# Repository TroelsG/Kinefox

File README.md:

# Kinefox
The wildlife tracker powered by kinetic energy

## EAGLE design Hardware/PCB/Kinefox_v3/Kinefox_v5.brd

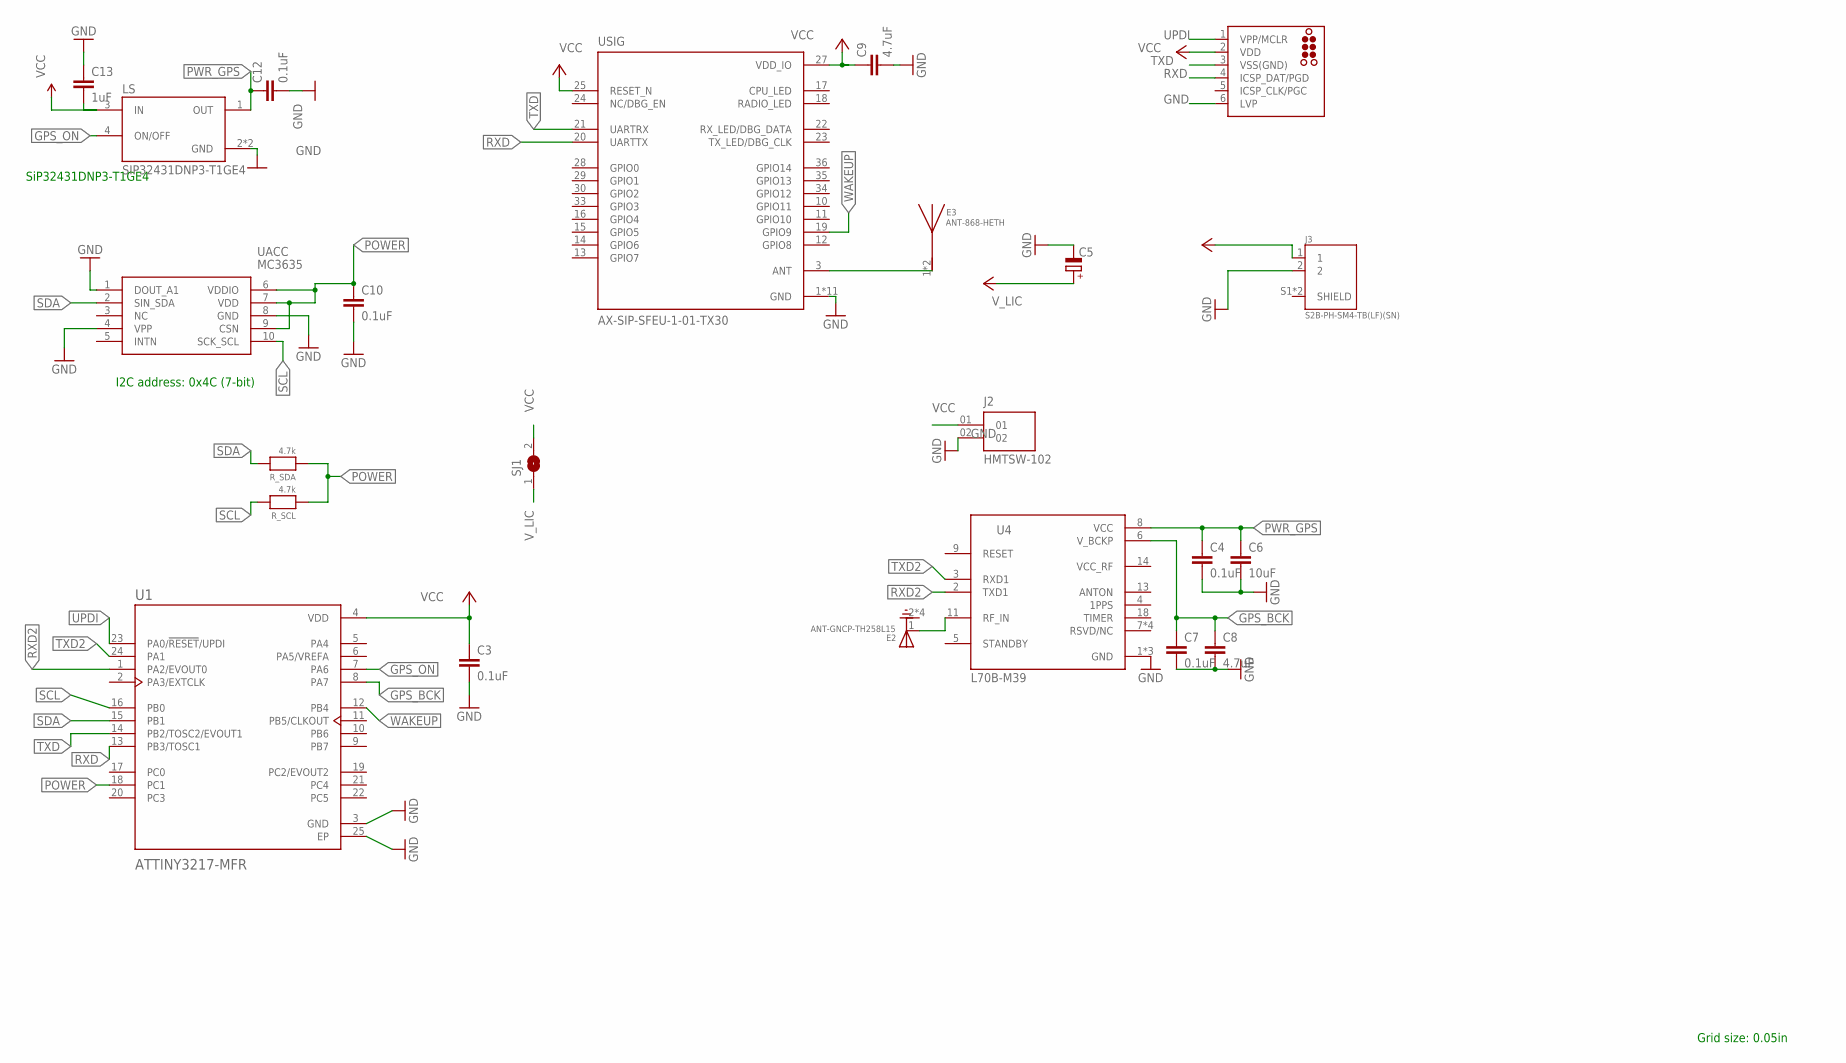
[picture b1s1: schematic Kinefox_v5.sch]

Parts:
C3, C4, C7, C10, C12: 0.1uF; C0402
C5: CPOL-EUE3.5-8; E3,5-8
C6: 10uF; C0402
C8, C9: 4.7uF; C0402
C13: 1uF; C0402
E2: ANT-GNCP-TH258L15; XCVR_ANT-GNCP-TH258L15
E3: ANT-868-HETH; XDCR_ANT-868-HETH
J1: TC2030-MCP-NL
J2: HMTSW-102; SAMTEC_HMTSW-102-XX-X-S-XXX
J3: S2B-PH-SM4-TB(LF)(SN); JST_S2B-PH-SM4-TB(LF)(SN)
LS: SIP32431DNP3-T1GE4; SON50P120X160X60-5N
R_SCL: 4.7k; MICROBUILDER__0402
R_SDA: 4.7k; MICROBUILDER__0402
SJ1: SJ
U1: ATTINY3217-MFR; QFN50P400X400X90-25N
U4: L70B-M39; XCVR_L70B-M39
UACC: MC3635
USIG: AX-SIP-SFEU-1-01-TX30; IC_AX-SIP-SFEU-1-01-TX30

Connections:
GND: C3.2, C4.2, C5.-, C6.2, C7.2, C8.2, C9.2, C10.2, C12.2, C13.1, E2.2 (GND), E2.3 (GND), E2.4 (GND), E2.5 (GND), J1.6 (LVP), J2.02, J3.2, LS.2 (GND), LS.5 (GND), U1.3 (GND), U1.25 (EP), U4.1 (GND), U4.10 (GND), U4.12 (GND), UACC.1 (DOUT_A1), UACC.4 (VPP), UACC.8 (GND), USIG.1 (GND), USIG.2 (GND), USIG.4 (GND), USIG.6 (GND), USIG.26 (GND), USIG.P1 (GND), USIG.P2 (GND), USIG.P3 (GND), USIG.P4 (GND), USIG.P5 (GND), USIG.P6 (GND)
GPS_ANT: E2.1 (FEEDING), U4.11 (RF_IN)
GPS_BCK: C7.1, C8.1, U1.8 (PA7), U4.6 (V_BCKP)
GPS_ON: LS.4 (ON/OFF), U1.7 (PA6)
POWER: C10.1, R_SCL.1, R_SDA.1, U1.18 (PC1), UACC.6 (VDDIO), UACC.7 (VDD), UACC.9 (CSN)
PWR_GPS: C4.1, C6.1, C12.1, LS.1 (OUT), U4.8 (VCC)
RXD: J1.4 (ICSP_DAT/PGD), U1.13 (PB3/TOSC1), USIG.20 (UARTTX)
RXD2: U1.1 (PA2/EVOUT0), U4.2 (TXD1)
SCL: R_SCL.2, U1.16 (PB0), UACC.10 (SCK_SCL)
SDA: R_SDA.2, U1.15 (PB1), UACC.2 (SIN_SDA)
SIG_ANT: E3.1, E3.3, USIG.3 (ANT)
TXD: J1.3 (VSS(GND)), U1.14 (PB2/TOSC2/EVOUT1), USIG.21 (UARTRX)
TXD2: U1.24 (PA1), U4.3 (RXD1)
UPDI: J1.1 (VPP/MCLR), U1.23 (PA0/!RESET!/UPDI)
VCC: C3.1, C9.1, C13.2, J1.2 (VDD), J2.01, J3.1, LS.3 (IN), SJ1.2, U1.4 (VDD), USIG.25 (RESET_N), USIG.27 (VDD_IO)
V_LIC: C5.+, SJ1.1
WAKEUP: U1.12 (PB4), USIG.19 (GPIO9)

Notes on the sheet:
Grid size: 0.05in
I2C address: 0x4C (7-bit)
SiP32431DNP3-T1GE4

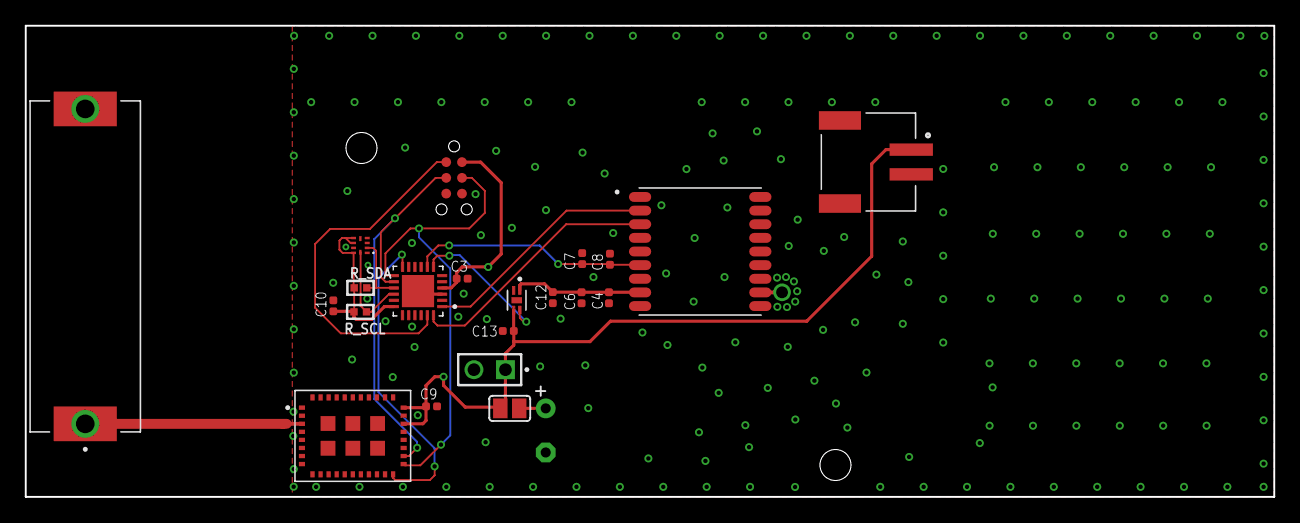
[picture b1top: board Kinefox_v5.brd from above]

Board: 4 copper layers, 100.7 x 38.0 mm, 23 parts (1 on the bottom side), 17 nets.

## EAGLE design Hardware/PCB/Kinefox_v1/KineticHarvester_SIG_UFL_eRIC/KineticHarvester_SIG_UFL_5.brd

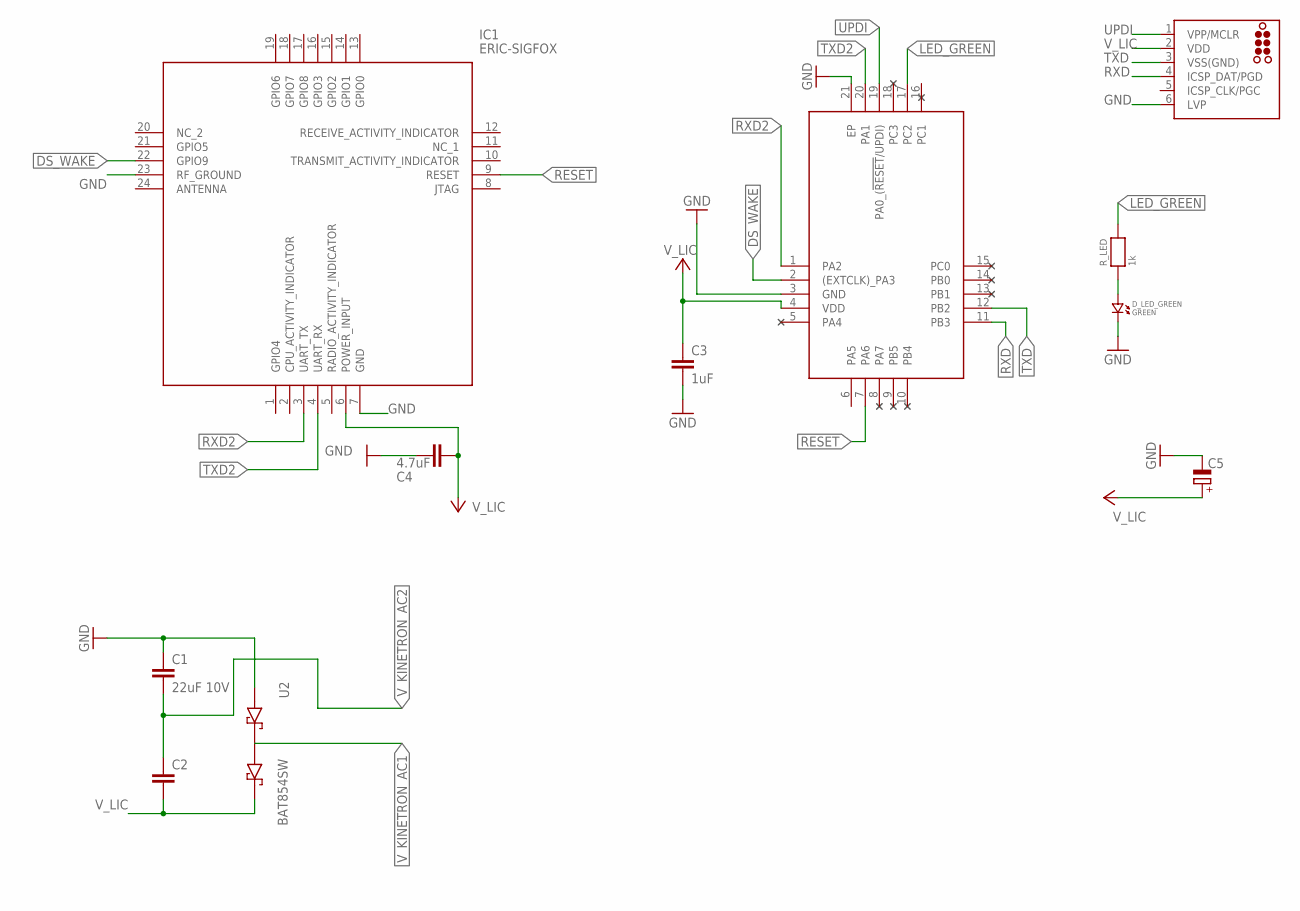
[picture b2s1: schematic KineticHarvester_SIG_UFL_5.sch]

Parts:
ATTINY: ATTINY1616-MFR; QFN40P300X300X90-21N
C1, C2: 22uF 10V; C0603
C3: 1uF; C0402
C4: 4.7uF; C0402
C5: CPOL-EUE3.5-8; E3,5-8
D_LED_GREEN: GREEN; CMONR_STANDARDPARTS_0402.LED
IC1: ERIC-SIGFOX; ERICSIGFOX
J1: TC2030-MCP-NL
R_LED: 1k; MICROBUILDER__0402MP
U2: BAT854SW; SOT323

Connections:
DS_WAKE: ATTINY.2 ((EXTCLK)_PA3), IC1.22 (GPIO9)
GND: ATTINY.3 (GND), ATTINY.21 (EP), C1.1, C3.2, C4.2, C5.-, D_LED_GREEN.P$2 (2), IC1.7 (GND), IC1.23 (RF_GROUND), J1.6 (LVP), U2.2 (PIN1)
LED_GREEN: ATTINY.17 (PC2), R_LED.2
unnamed: D_LED_GREEN.P$1 (1), R_LED.1
RESET: ATTINY.7 (PA6), IC1.9 (RESET)
RXD: ATTINY.11 (PB3), J1.4 (ICSP_DAT/PGD)
RXD2: ATTINY.1 (PA2), IC1.3 (UART_TX)
TXD: ATTINY.12 (PB2), J1.3 (VSS(GND))
TXD2: ATTINY.20 (PA1), IC1.4 (UART_RX)
UPDI: ATTINY.19 (PA0_(!RESET!/UPDI)), J1.1 (VPP/MCLR)
V_KINETRON_AC1: U2.1 (PIN3)
V_KINETRON_AC2: C1.2, C2.1
V_LIC: ATTINY.4 (VDD), C2.2, C3.1, C4.1, C5.+, IC1.6 (POWER_INPUT), J1.2 (VDD), U2.3 (PIN2)

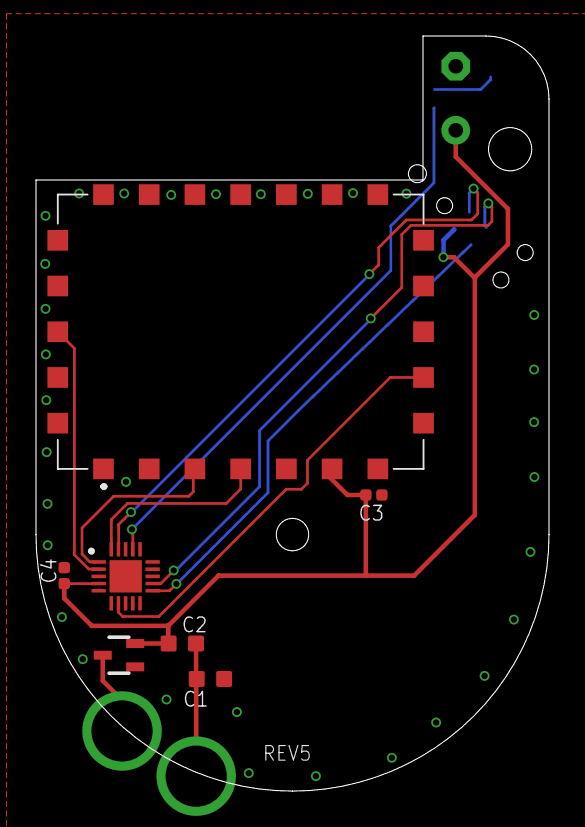
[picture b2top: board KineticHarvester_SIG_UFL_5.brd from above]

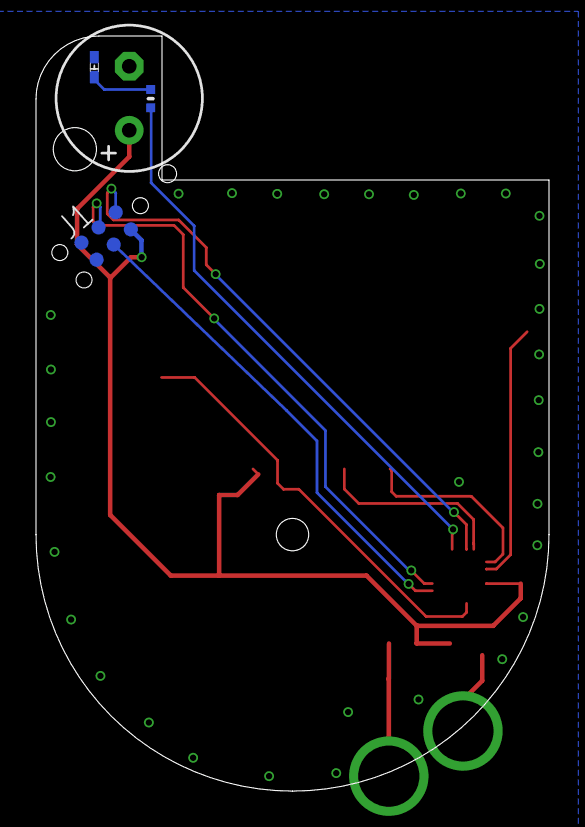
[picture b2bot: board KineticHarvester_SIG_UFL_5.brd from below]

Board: 2 copper layers, 28.5 x 42.0 mm, 11 parts (4 on the bottom side), 12 nets.

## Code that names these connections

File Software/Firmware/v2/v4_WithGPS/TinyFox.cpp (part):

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
void deviceInitPins() {
	// OUTPUT = lowest setting
	PORTA.DIR = (INPUT_DIR << PIN0_bp)	// PA0: UPDI
	| (OUTPUT_DIR << PIN1_bp)			// PA1: TXD2
	| (INPUT_DIR << PIN2_bp)			// PA2: RXD2
	| (OUTPUT_DIR << PIN3_bp)			// PA3: LED_RED
	| (OUTPUT_DIR << PIN4_bp)			// PA4: START
	| (OUTPUT_DIR << PIN5_bp)			// PA5: VOLT_MEAS
	| (OUTPUT_DIR << PIN6_bp)			// PA6: GPS_ON
	| (OUTPUT_DIR << PIN7_bp);			// PA7: GPS_BCK
	PORTB.DIR = (OUTPUT_DIR << PIN0_bp)	// PB0: SCL
	| (OUTPUT_DIR << PIN1_bp)			// PB1: SDA
	| (OUTPUT_DIR << PIN2_bp)			// PB2: TXD
	| (INPUT_DIR << PIN3_bp)			// PB3: RXD
	| (OUTPUT_DIR << PIN4_bp)	     	// PB4: WAKEUP
	| (OUTPUT_DIR << PIN5_bp)           // PB5: **UNUSED**
    | (OUTPUT_DIR << PIN6_bp)			// PB6: **UNUSED**
	| (OUTPUT_DIR << PIN7_bp);			// PB7: **UNUSED**
	PORTC.DIR = (OUTPUT_DIR << PIN0_bp)	// PC0: **UNUSED**
	| (OUTPUT_DIR << PIN1_bp)		// PC1: POWER
	| (OUTPUT_DIR << PIN2_bp)			// PC2: LED_GREEN
	| (OUTPUT_DIR << PIN3_bp)			// PC3: **UNUSED**
	| (OUTPUT_DIR << PIN4_bp)			// PC4: **UNUSED**
	| (OUTPUT_DIR << PIN5_bp);	     	// PC5: **UNUSED**
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
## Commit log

2022-10-19 Begin
2022-10-19 Creo files
2022-10-19 Firmware
2022-10-19 Data
2022-10-19 Masters thesis
2022-10-19 Rearranging
2022-10-19 Inch to mm
2023-05-02 Kinefox V1 and V2
2023-05-02 Change language on folder names and delete folders related to publication
2023-05-02 Rearrange folders
2023-05-02 Deleted old folder

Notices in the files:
parts and their libraries:
tag-connect: ©2009 ROFA.cz - modified and updated by Robert Darlington ‹rdarlington@gmail.com›
SparkFun-PowerSymbols: Licensing: Creative Commons ShareAlike 4.0 International - https://creativecommons.org/licenses/by-sa/4.0
